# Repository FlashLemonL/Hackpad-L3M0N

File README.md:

# Hackpad-L3M0N
My first ever hardware, CAD and 3D modelled project. it is a macro pad that i need to use since my keyboard is missing some keys and macros will be useful to open up study resources.

3D Model of PCB

### Parts in the build
- 6x Cherry MX Switches
- 1x 0.91 inch OLED display
- 1x XIAO RP2040
- 6x Blank DSA Keycaps
- 1x EC11 Rotary encoders
- 4x M3x16 Bolt
- 4x M3 Heatset

Schematic            |  PCB         |   Assembled Case
:-------------------------:|:-------------------------:|:-------------------------:|
    |    | 

Assembled Case With Top Off

Front Expanded            |  Back Expanded         |   Front Corner   |  Back Corner         |
:-------------------------:|:-------------------------:|:-------------------------:|:-------------------------:|
     |        |        |        |

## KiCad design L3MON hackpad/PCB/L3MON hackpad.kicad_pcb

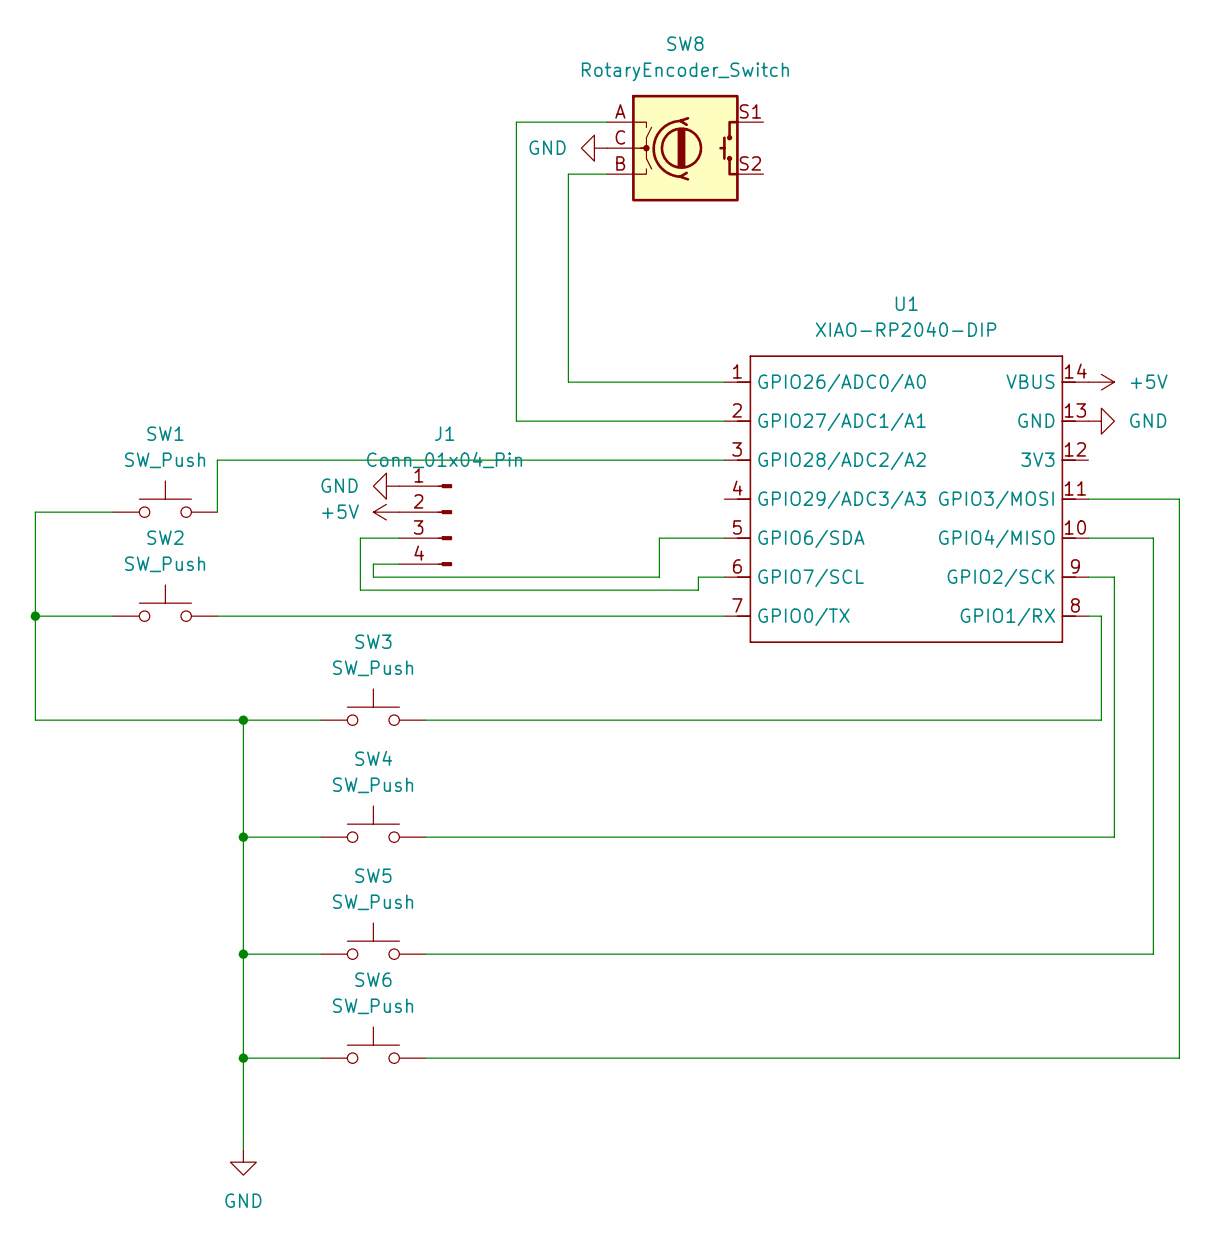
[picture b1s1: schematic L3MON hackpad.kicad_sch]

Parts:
J1: Conn_01x04_Pin; SSD1306-0.91-OLED-4pin-128x32
SW1, SW2, SW3, SW4, SW5, SW6: SW_Push; SW_Cherry_MX_1.00u_PCB
SW8: RotaryEncoder_Switch; RotaryEncoder_Alps_EC11E-Switch_Vertical_H20mm
U1: XIAO-RP2040-DIP

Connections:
+5V: J1.2, U1.14 (VBUS)
GND: J1.1, SW1.1, SW2.1, SW3.1, SW4.1, SW5.1, SW6.1, SW8.C, U1.13 (GND)
unnamed: J1.3, U1.6 (GPIO7/SCL)
unnamed: J1.4, U1.5 (GPIO6/SDA)
unnamed: SW2.2, U1.7 (GPIO0/TX)
unnamed: SW3.2, U1.8 (GPIO1/RX)
unnamed: SW4.2, U1.9 (GPIO2/SCK)
unnamed: SW6.2, U1.11 (GPIO3/MOSI)
unnamed: SW5.2, U1.10 (GPIO4/MISO)
unnamed: SW8.B, U1.1 (GPIO26/ADC0/A0)
unnamed: SW8.A, U1.2 (GPIO27/ADC1/A1)
unnamed: SW1.2, U1.3 (GPIO28/ADC2/A2)

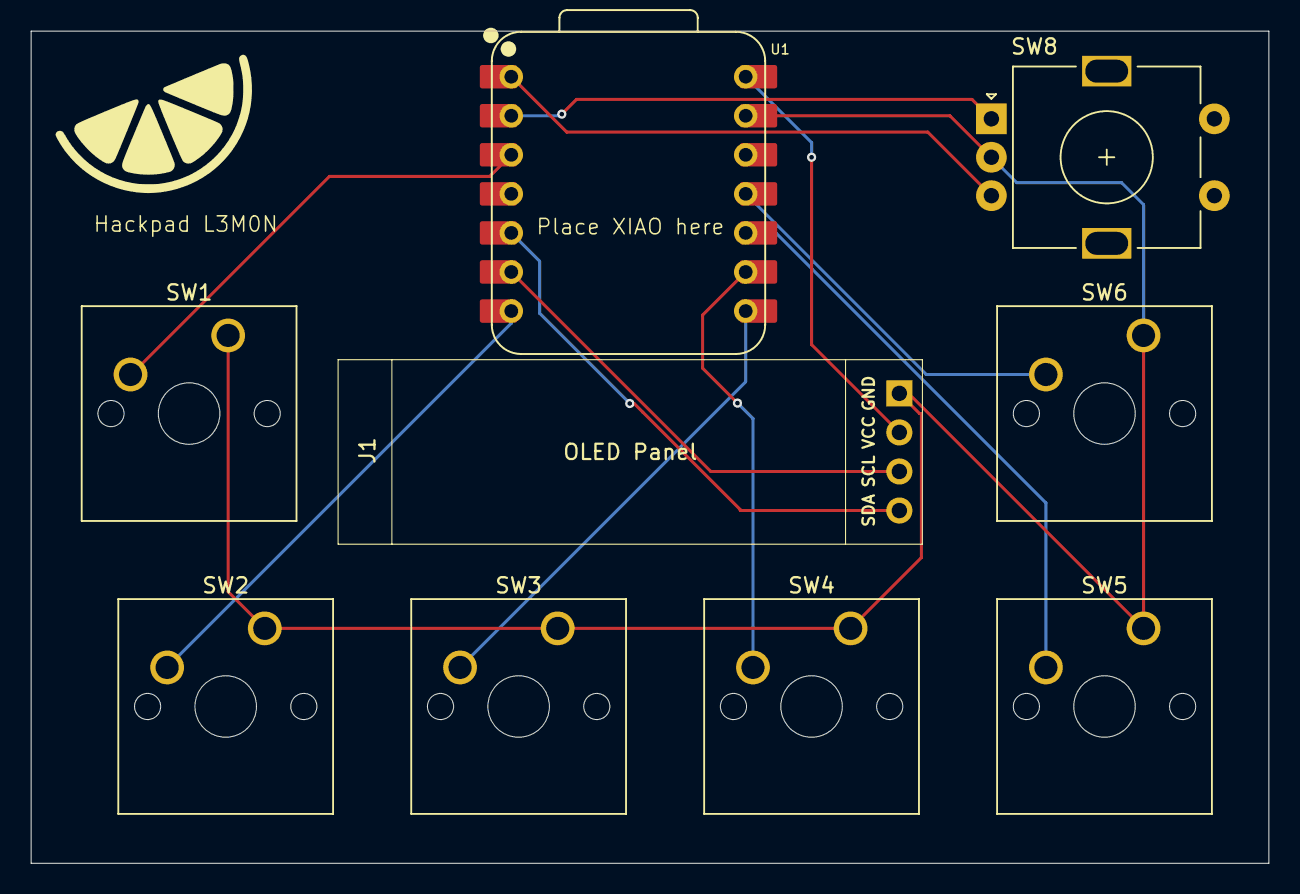
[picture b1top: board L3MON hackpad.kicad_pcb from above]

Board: 2 copper layers, 80.5 x 54.1 mm, 9 parts (0 on the bottom side), 12 nets.

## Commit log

2025-11-25 Added the switches and XIAO RP2040
2025-11-25 added the wires from the switch to the XIAO RP2040 and added a rotary encoder
2025-11-25 backup commit just in case
2025-11-27 added more things
2025-11-27 wiring
2025-11-30 made the pcb
2025-11-30 finished pcb
2025-12-03 complete pcb
2025-12-03 Uploaded 3D model
2025-12-04 Added 3d model of case
2025-12-04 editing readme
2025-12-05 further edits
2025-12-07 finished the code
2025-12-07 Moved folders out of inside folder
2025-12-07 added new images
2025-12-07 added pcb footprints
2025-12-08 updated models and added assets
2025-12-08 Finished the README.md
2025-12-08 added gerber file
